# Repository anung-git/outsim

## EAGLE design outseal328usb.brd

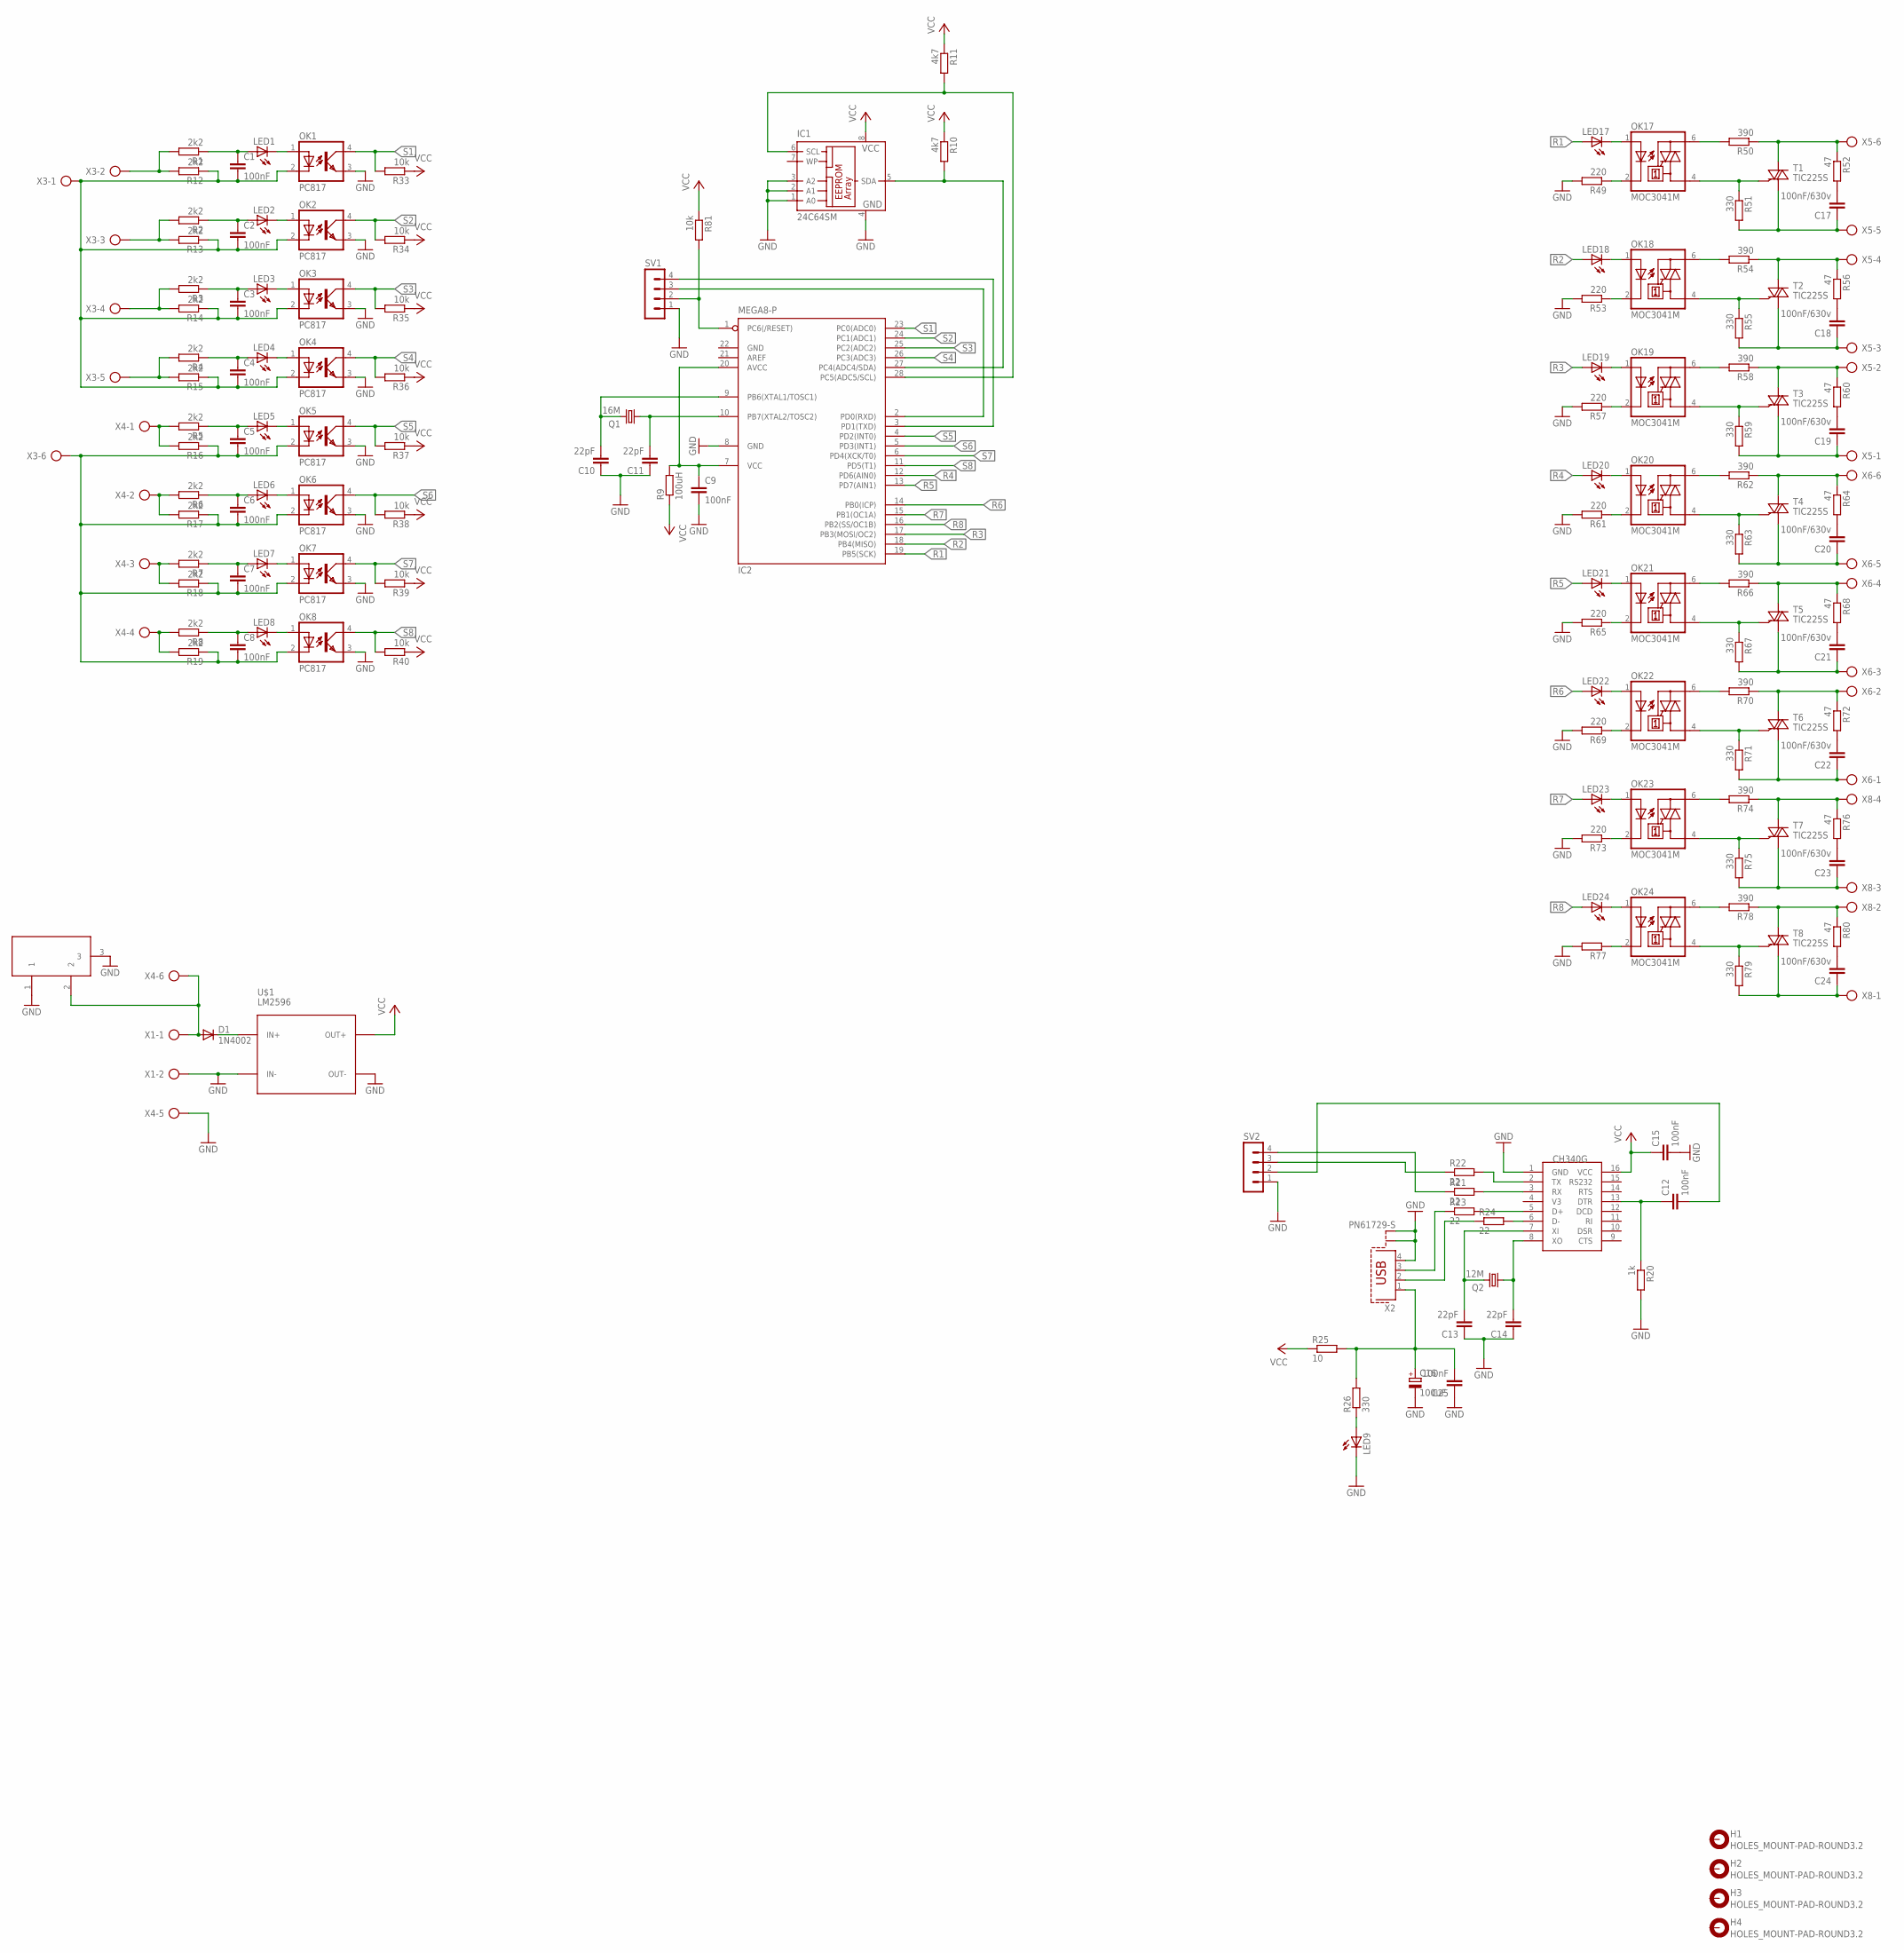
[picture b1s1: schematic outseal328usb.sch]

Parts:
C1, C2, C3, C4, C5, C6, C7, C8, C9, C12, C15, C25: 100nF; C050-025X075
C10, C11, C13, C14: 22pF; C025-025X050
C16: 100uF; E5-4
C17, C18, C19, C20, C21, C22, C23, C24: 100nF/630v; C102-043X133
D1: 1N4002; DO35-10@1
H1, H2, H3, H4: HOLES_MOUNT-PAD-ROUND3.2; HOLES_3,2-PAD
IC1: 24C64SM; SO-08M
IC2: MEGA8-P; DIL28-3
LED1, LED2, LED3, LED4, LED5, LED6, LED7, LED8, LED9, LED17, LED18, LED19, LED20, LED21, LED22, LED23, LED24: LED5MM
OK1, OK2, OK3, OK4, OK5, OK6, OK7, OK8: PC817; DIL04
OK17, OK18, OK19, OK20, OK21, OK22, OK23, OK24: MOC3041M; DIL06
Q1: 16M; HC49/S
Q2: 12M; HC49/S
R1, R2, R3, R4, R5, R6, R7, R8, R12, R13, R14, R15, R16, R17, R18, R19: 2k2; 0207/10
R9: 100uH; 0207/10
R10, R11: 4k7; 0207/10
R20: 1k; 0207/10
R21, R22, R23, R24: 22; 0207/10
R25: 10; 0207/10
R26, R51, R55, R59, R63, R67, R71, R75, R79: 330; 0207/10
R33, R34, R35, R36, R37, R38, R39, R40, R81: 10k; 0207/10
R49, R53, R57, R61, R65, R69, R73: 220; 0207/10
R50, R54, R58, R62, R66, R70, R74, R78: 390; 0207/10
R52, R56, R60, R64, R68, R72, R76, R80: 47; 0207/10
R77: R-EU_0207/10; 0207/10
SV1, SV2: MA04-1
T1, T2, T3, T4, T5, T6, T7, T8: TIC225S; TO220DS
U$1: LM2596; DC-DC-STEP-DOWN-LM2596
U$2: 12v-24v; POWERSUPPLY_DC-21MM
U$3: CH340G; SOIC16
X1: AK500/2
X2: PN61729-S
X3, X4, X5, X6: AK500/6
X8: AK500/4

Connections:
GND: C9.2, C10.1, C11.1, C13.1, C14.1, C15.2, C16.-, C25.1, IC1.1 (A0), IC1.2 (A1), IC1.3 (A2), IC1.4 (GND), IC2.8 (GND), IC2.22 (GND), LED9.K (C), OK1.3 (EMIT), OK2.3 (EMIT), OK3.3 (EMIT), OK4.3 (EMIT), OK5.3 (EMIT), OK6.3 (EMIT), OK7.3 (EMIT), OK8.3 (EMIT), R20.2, R49.2, R53.2, R57.2, R61.2, R65.2, R69.2, R73.2, R77.2, SV1.1, SV2.1, U$1.IN-, U$1.OUT-, U$2.1, U$2.3, U$3.1 (GND), X1.2, X2.4, X2.S1, X2.S2, X4.5
M8RXD: R22.1, SV2.3
M8TXD: R21.1, SV2.4
unnamed: C1.1, LED1.A, R1.1
unnamed: C2.1, LED2.A, R2.1
unnamed: C3.1, LED3.A, R3.1
unnamed: C4.1, LED4.A, R4.1
unnamed: C5.1, LED5.A, R5.1
unnamed: C6.1, LED6.A, R6.1
unnamed: C7.1, LED7.A, R7.1
unnamed: C8.1, LED8.A, R8.1
unnamed: C11.2, IC2.10 (PB7(XTAL2/TOSC2)), Q1.1
unnamed: C10.2, IC2.9 (PB6(XTAL1/TOSC1)), Q1.2
unnamed: IC1.5 (SDA), IC2.27 (PC4(ADC4/SDA)), R10.2
unnamed: LED1.K (C), OK1.1 (A)
unnamed: LED2.K (C), OK2.1 (A)
unnamed: LED3.K (C), OK3.1 (A)
unnamed: LED4.K (C), OK4.1 (A)
unnamed: LED5.K (C), OK5.1 (A)
unnamed: LED6.K (C), OK6.1 (A)
unnamed: LED7.K (C), OK7.1 (A)
unnamed: LED8.K (C), OK8.1 (A)
unnamed: IC2.2 (PD0(RXD)), SV1.3
unnamed: D1.A, U$2.2, X1.1, X4.6
unnamed: D1.C, U$1.IN+
unnamed: C9.1, IC2.7 (VCC), IC2.20 (AVCC), R9.2
unnamed: IC1.6 (SCL), IC2.28 (PC5(ADC5/SCL)), R11.2
unnamed: C1.2, C2.2, C3.2, C4.2, OK1.2 (C), OK2.2 (C), OK3.2 (C), OK4.2 (C), R12.1, R13.1, R14.1, R15.1, X3.1
unnamed: C12.2, SV2.2
unnamed: C12.1, R20.1, U$3.13 (DTR)
unnamed: R22.2, U$3.2 (TX)
unnamed: C5.2, C6.2, C7.2, C8.2, OK5.2 (C), OK6.2 (C), OK7.2 (C), OK8.2 (C), R16.1, R17.1, R18.1, R19.1, X3.6
unnamed: R21.2, U$3.3 (RX)
unnamed: IC2.3 (PD1(TXD)), SV1.4
unnamed: C14.2, Q2.1, U$3.8 (XO)
unnamed: C13.2, Q2.2, U$3.7 (XI)
unnamed: R24.1, X2.2
unnamed: R23.1, X2.3
unnamed: R23.2, U$3.5 (D+)
unnamed: R8.2, R19.2, X4.4
unnamed: R7.2, R18.2, X4.3
unnamed: R6.2, R17.2, X4.2
unnamed: R5.2, R16.2, X4.1
unnamed: R4.2, R15.2, X3.5
unnamed: R3.2, R14.2, X3.4
unnamed: R2.2, R13.2, X3.3
unnamed: R1.2, R12.2, X3.2
unnamed: R24.2, U$3.6 (D-)
unnamed: C16.+, C25.2, R25.2, R26.2, X2.1
unnamed: LED9.A, R26.1
unnamed: OK17.2 (C), R49.1
unnamed: LED17.K (C), OK17.1 (A)
unnamed: OK17.6 (A2), R50.2
unnamed: R50.1, R52.1, T1.A2, X5.6
unnamed: OK17.4 (A1), R51.1, T1.G
unnamed: C17.1, R51.2, T1.A1, X5.5
unnamed: C17.2, R52.2
unnamed: LED18.K (C), OK18.1 (A)
unnamed: OK18.2 (C), R53.1
unnamed: OK18.6 (A2), R54.2
unnamed: R54.1, R56.1, T2.A2, X5.4
unnamed: OK18.4 (A1), R55.1, T2.G
unnamed: C18.1, R55.2, T2.A1, X5.3
unnamed: C18.2, R56.2
unnamed: LED19.K (C), OK19.1 (A)
unnamed: OK19.2 (C), R57.1
unnamed: OK19.6 (A2), R58.2
unnamed: R58.1, R60.1, T3.A2, X5.2
unnamed: OK19.4 (A1), R59.1, T3.G
unnamed: C19.1, R59.2, T3.A1, X5.1
unnamed: C19.2, R60.2
unnamed: LED20.K (C), OK20.1 (A)
unnamed: OK20.2 (C), R61.1
unnamed: OK20.6 (A2), R62.2
unnamed: R62.1, R64.1, T4.A2, X6.6
unnamed: OK20.4 (A1), R63.1, T4.G
unnamed: C20.1, R63.2, T4.A1, X6.5
unnamed: C20.2, R64.2
unnamed: LED21.K (C), OK21.1 (A)
unnamed: OK21.2 (C), R65.1
unnamed: OK21.6 (A2), R66.2
unnamed: R66.1, R68.1, T5.A2, X6.4
unnamed: OK21.4 (A1), R67.1, T5.G
unnamed: C21.1, R67.2, T5.A1, X6.3
unnamed: C21.2, R68.2
unnamed: LED22.K (C), OK22.1 (A)
unnamed: OK22.2 (C), R69.1
unnamed: OK22.6 (A2), R70.2
unnamed: R70.1, R72.1, T6.A2, X6.2
unnamed: OK22.4 (A1), R71.1, T6.G
unnamed: C22.1, R71.2, T6.A1, X6.1
unnamed: C22.2, R72.2
unnamed: LED23.K (C), OK23.1 (A)
unnamed: OK23.2 (C), R73.1
unnamed: OK23.6 (A2), R74.2
unnamed: R74.1, R76.1, T7.A2, X8.4
unnamed: OK23.4 (A1), R75.1, T7.G
unnamed: C23.1, R75.2, T7.A1, X8.3
unnamed: C23.2, R76.2
unnamed: LED24.K (C), OK24.1 (A)
unnamed: OK24.2 (C), R77.1
unnamed: OK24.6 (A2), R78.2
unnamed: R78.1, R80.1, T8.A2, X8.2
unnamed: OK24.4 (A1), R79.1, T8.G
unnamed: C24.1, R79.2, T8.A1, X8.1
unnamed: C24.2, R80.2
unnamed: IC2.1 (PC6(/RESET)), R81.2, SV1.2
R1: IC2.19 (PB5(SCK)), LED17.A
R2: IC2.18 (PB4(MISO)), LED18.A
R3: IC2.17 (PB3(MOSI/OC2)), LED19.A
R4: IC2.12 (PD6(AIN0)), LED20.A
R5: IC2.13 (PD7(AIN1)), LED21.A
R6: IC2.14 (PB0(ICP)), LED22.A
R7: IC2.15 (PB1(OC1A)), LED23.A
R8: IC2.16 (PB2(SS/OC1B)), LED24.A
S1: IC2.23 (PC0(ADC0)), OK1.4 (COL), R33.2
S2: IC2.24 (PC1(ADC1)), OK2.4 (COL), R34.2
S3: IC2.25 (PC2(ADC2)), OK3.4 (COL), R35.2
S4: IC2.26 (PC3(ADC3)), OK4.4 (COL), R36.2
S5: IC2.4 (PD2(INT0)), OK5.4 (COL), R37.2
S6: IC2.5 (PD3(INT1)), OK6.4 (COL), R38.2
S7: IC2.6 (PD4(XCK/T0)), OK7.4 (COL), R39.2
S8: IC2.11 (PD5(T1)), OK8.4 (COL), R40.2
VCC: C15.1, IC1.8 (VCC), R9.1, R10.1, R11.1, R25.1, R33.1, R34.1, R35.1, R36.1, R37.1, R38.1, R39.1, R40.1, R81.1, U$1.OUT+, U$3.16 (VCC)

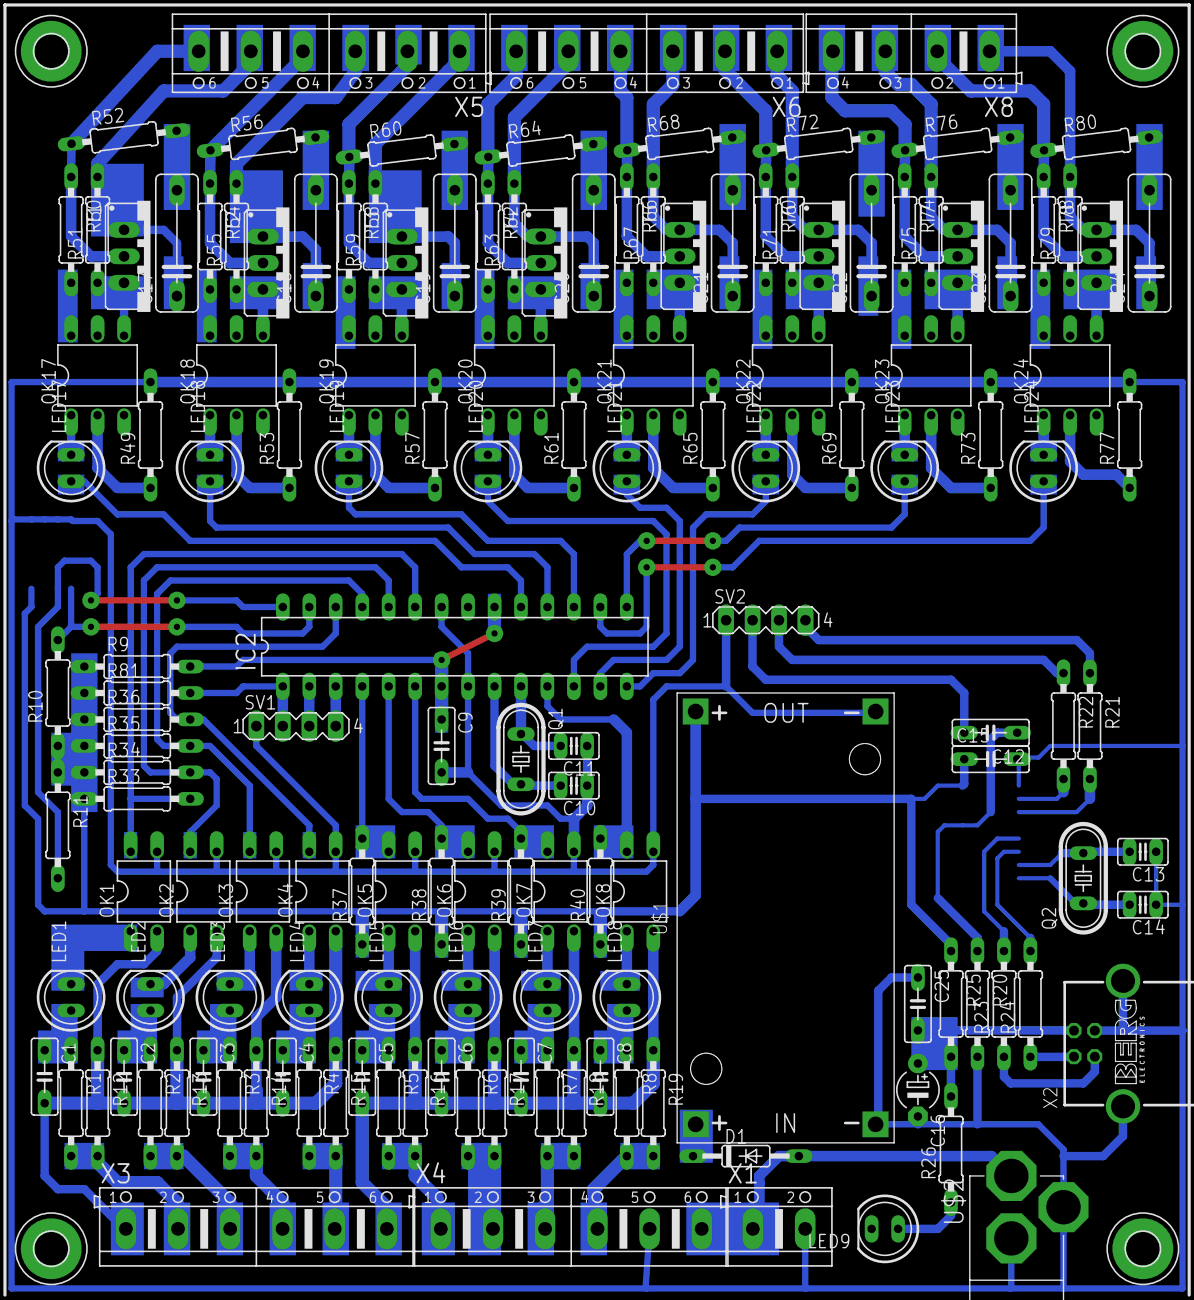
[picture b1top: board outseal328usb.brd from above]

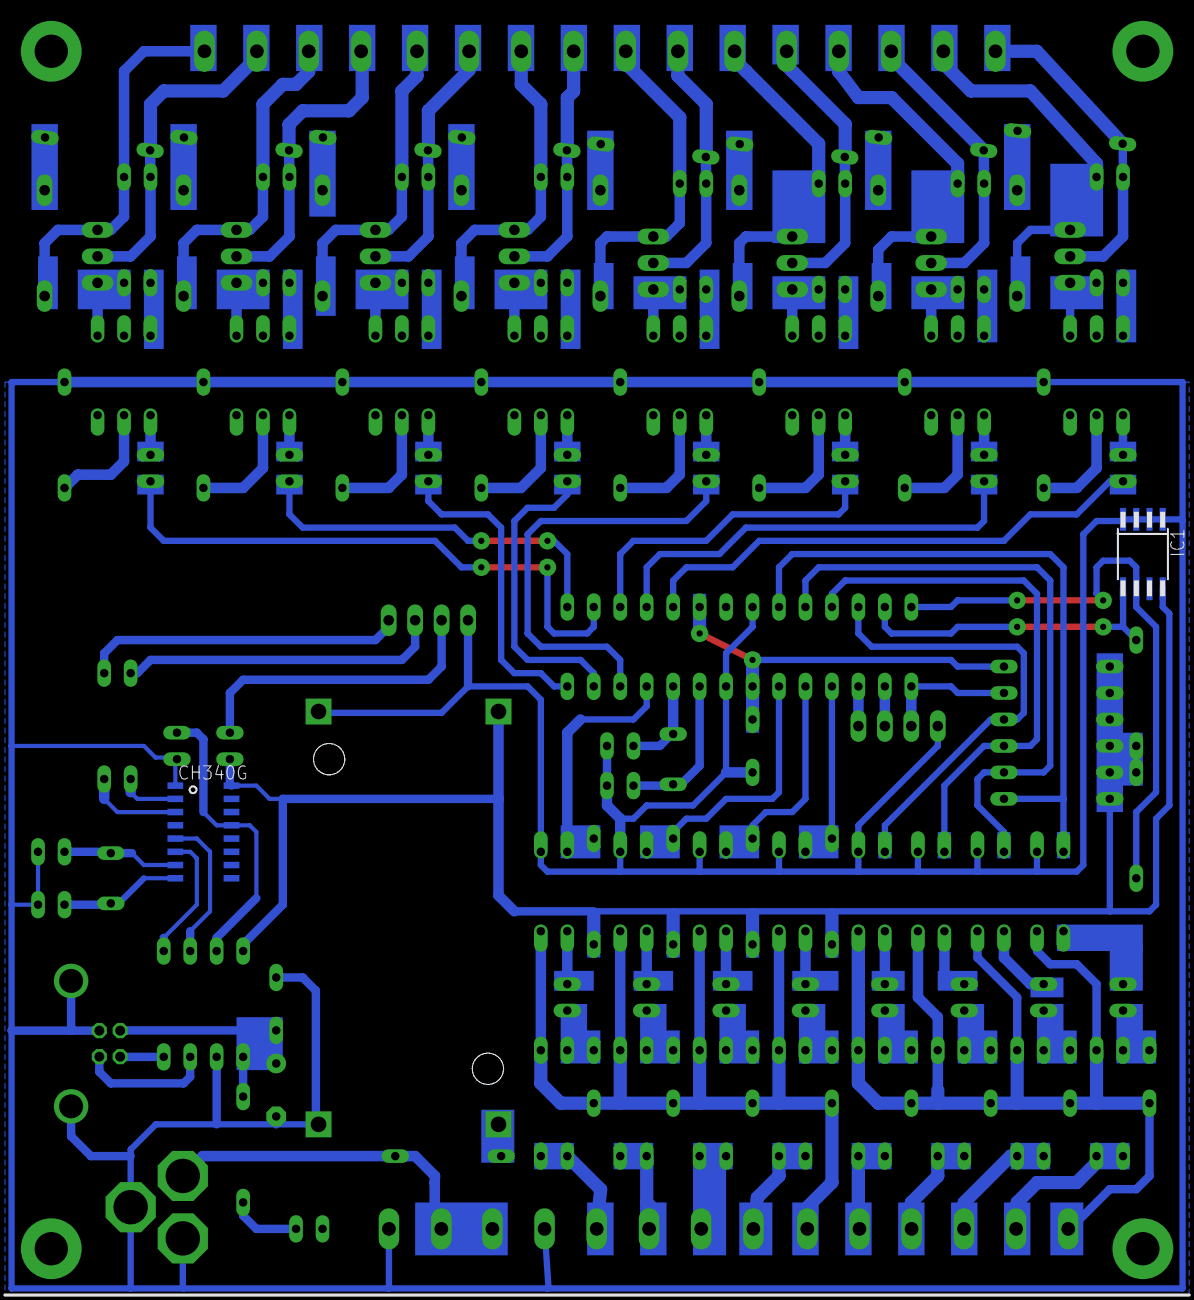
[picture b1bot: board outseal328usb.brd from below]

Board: 2 copper layers, 154 parts (2 on the bottom side), 124 nets.

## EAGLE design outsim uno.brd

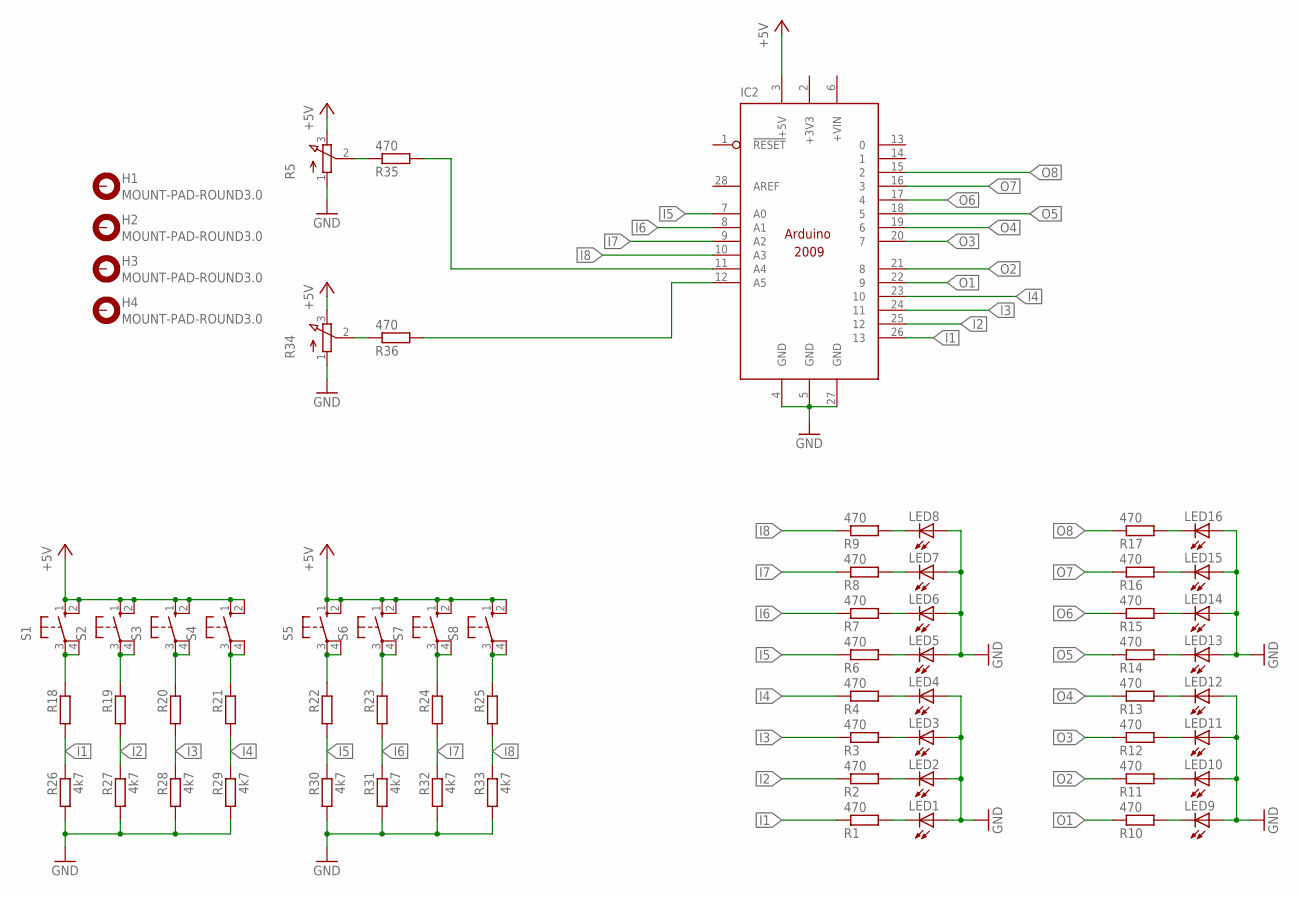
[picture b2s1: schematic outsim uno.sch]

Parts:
H1, H2, H3, H4: MOUNT-PAD-ROUND3.0; 3,0-PAD
IC2: ARDUINO2009_12; ARDUINO2009_2
LED1, LED2, LED3, LED4, LED5, LED6, LED7, LED8, LED9, LED10, LED11, LED12, LED13, LED14, LED15, LED16: LED5MM
R1, R2, R3, R4, R6, R7, R8, R9, R10, R11, R12, R13, R14, R15, R16, R17, R35, R36: 470; 0207/10
R5, R34: 3RP/1610N
R18, R19, R20, R21, R22, R23, R24, R25: R-EU_0207/10; 0207/10
R26, R27, R28, R29, R30, R31, R32, R33: 4k7; 0207/10
S1, S2, S3, S4, S5, S6, S7, S8: 10-XX; B3F-10XX

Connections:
+3V3: IC2.2 (+3V3)
+5V: IC2.3 (+5V), R5.3 (E), R34.3 (E), S1.1 (S), S1.2 (S1), S2.1 (S), S2.2 (S1), S3.1 (S), S3.2 (S1), S4.1 (S), S4.2 (S1), S5.1 (S), S5.2 (S1), S6.1 (S), S6.2 (S1), S7.1 (S), S7.2 (S1), S8.1 (S), S8.2 (S1)
GND: IC2.4 (GND), IC2.5 (GND), IC2.27 (GND), LED1.A, LED2.A, LED3.A, LED4.A, LED5.A, LED6.A, LED7.A, LED8.A, LED9.A, LED10.A, LED11.A, LED12.A, LED13.A, LED14.A, LED15.A, LED16.A, R5.1 (A), R26.2, R27.2, R28.2, R29.2, R30.2, R31.2, R32.2, R33.2, R34.1 (A)
I1: IC2.26 (13), R1.1, R18.2, R26.1
I2: IC2.25 (12), R2.1, R19.2, R27.1
I3: IC2.24 (11), R3.1, R20.2, R28.1
I4: IC2.23 (10), R4.1, R21.2, R29.1
I5: IC2.7 (A0), R6.1, R22.2, R30.1
I6: IC2.8 (A1), R7.1, R23.2, R31.1
I7: IC2.9 (A2), R8.1, R24.2, R32.1
I8: IC2.10 (A3), R9.1, R25.2, R33.1
unnamed: R34.2 (S), R36.1
unnamed: LED5.K (C), R6.2
unnamed: LED6.K (C), R7.2
unnamed: LED7.K (C), R8.2
unnamed: LED1.K (C), R1.2
unnamed: LED2.K (C), R2.2
unnamed: LED3.K (C), R3.2
unnamed: LED4.K (C), R4.2
unnamed: IC2.12 (A5), R36.2
unnamed: R20.1, S3.3, S3.4 (P1)
unnamed: LED8.K (C), R9.2
unnamed: LED9.K (C), R10.2
unnamed: LED10.K (C), R11.2
unnamed: LED11.K (C), R12.2
unnamed: LED12.K (C), R13.2
unnamed: LED13.K (C), R14.2
unnamed: R18.1, S1.3, S1.4 (P1)
unnamed: R19.1, S2.3, S2.4 (P1)
unnamed: LED14.K (C), R15.2
unnamed: LED15.K (C), R16.2
unnamed: LED16.K (C), R17.2
unnamed: IC2.11 (A4), R35.2
unnamed: R5.2 (S), R35.1
unnamed: R21.1, S4.3, S4.4 (P1)
unnamed: R22.1, S5.3, S5.4 (P1)
unnamed: R23.1, S6.3, S6.4 (P1)
unnamed: R24.1, S7.3, S7.4 (P1)
unnamed: R25.1, S8.3, S8.4 (P1)
O1: IC2.22 (9), R10.1
O2: IC2.21 (8), R11.1
O3: IC2.20 (7), R12.1
O4: IC2.19 (6), R13.1
O5: IC2.18 (5), R14.1
O6: IC2.17 (4), R15.1
O7: IC2.16 (3), R16.1
O8: IC2.15 (2), R17.1

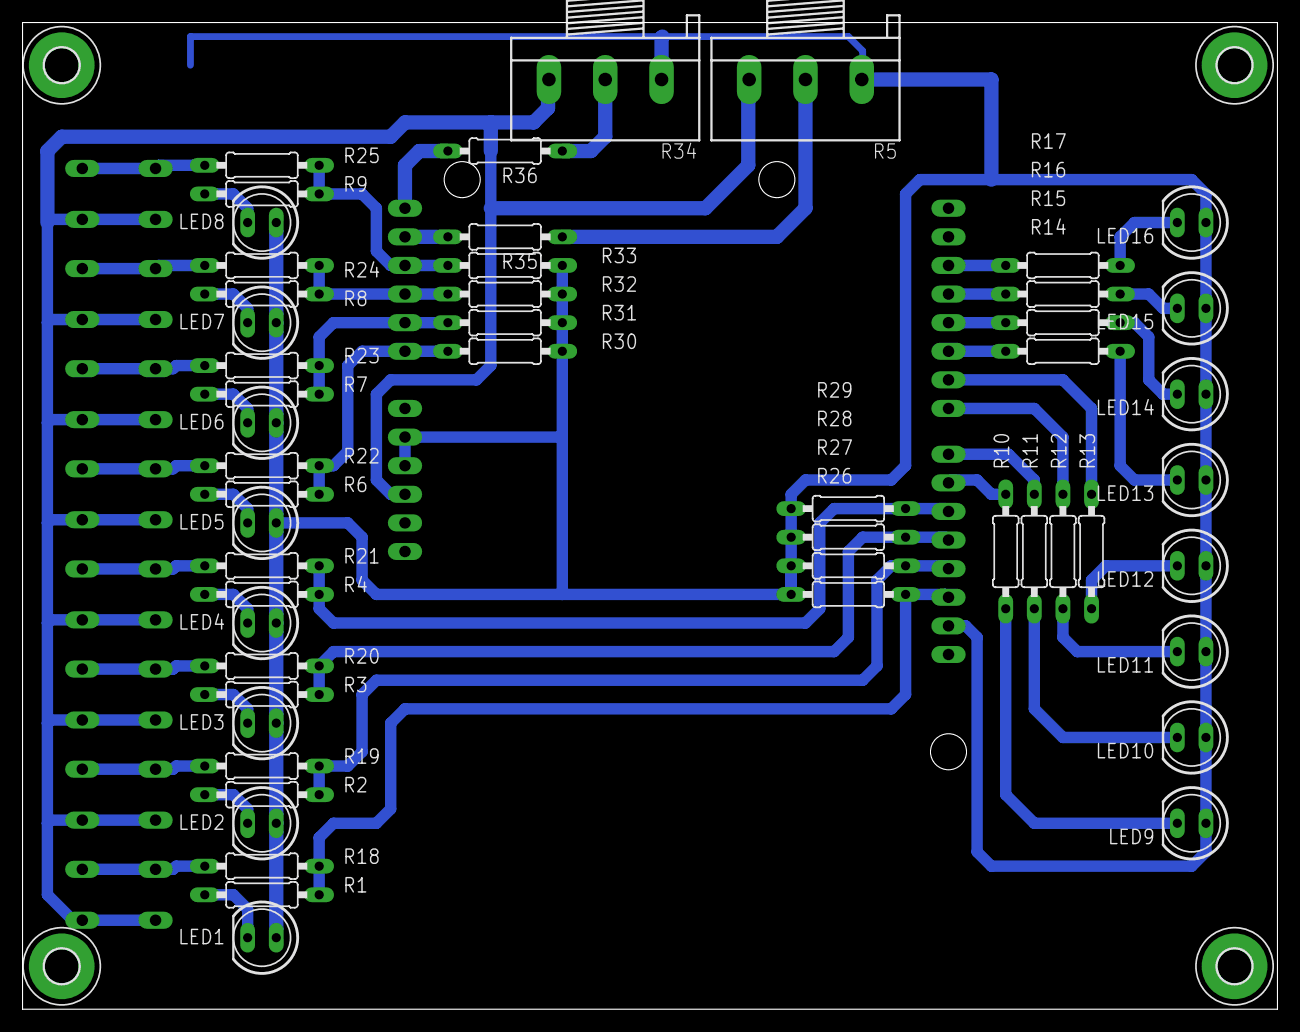
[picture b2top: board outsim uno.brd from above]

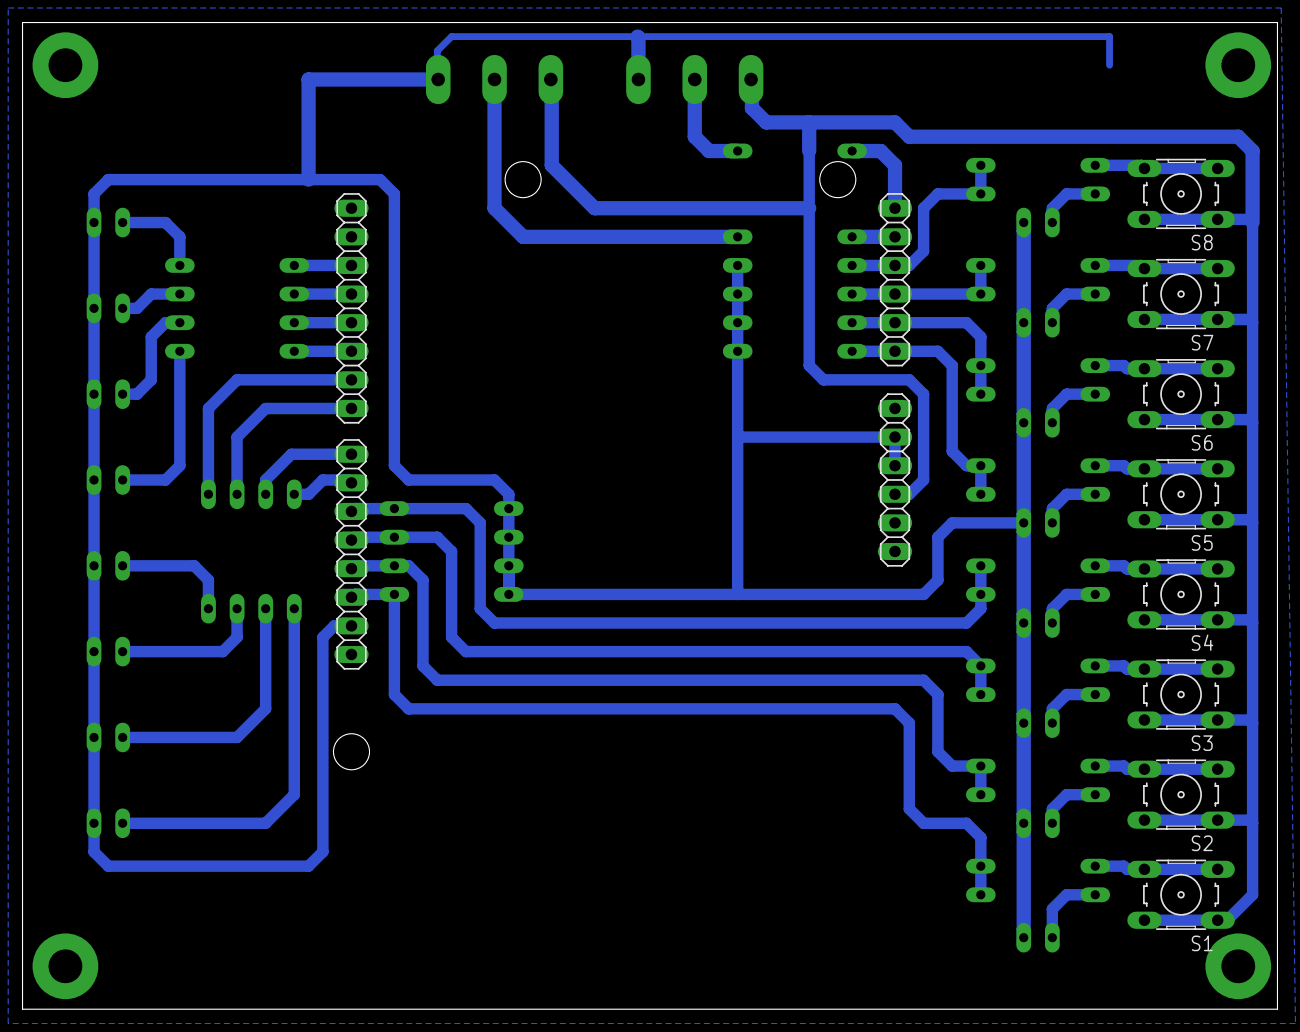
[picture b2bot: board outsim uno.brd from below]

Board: 2 copper layers, 111.4 x 87.6 mm, 65 parts (9 on the bottom side), 46 nets.

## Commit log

2021-01-07 upload

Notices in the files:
parts and their libraries:
diy-modules: Released under the Creative Commons Attribution 4.0 International License: http://creativecommons.org/licenses/by/4.0
